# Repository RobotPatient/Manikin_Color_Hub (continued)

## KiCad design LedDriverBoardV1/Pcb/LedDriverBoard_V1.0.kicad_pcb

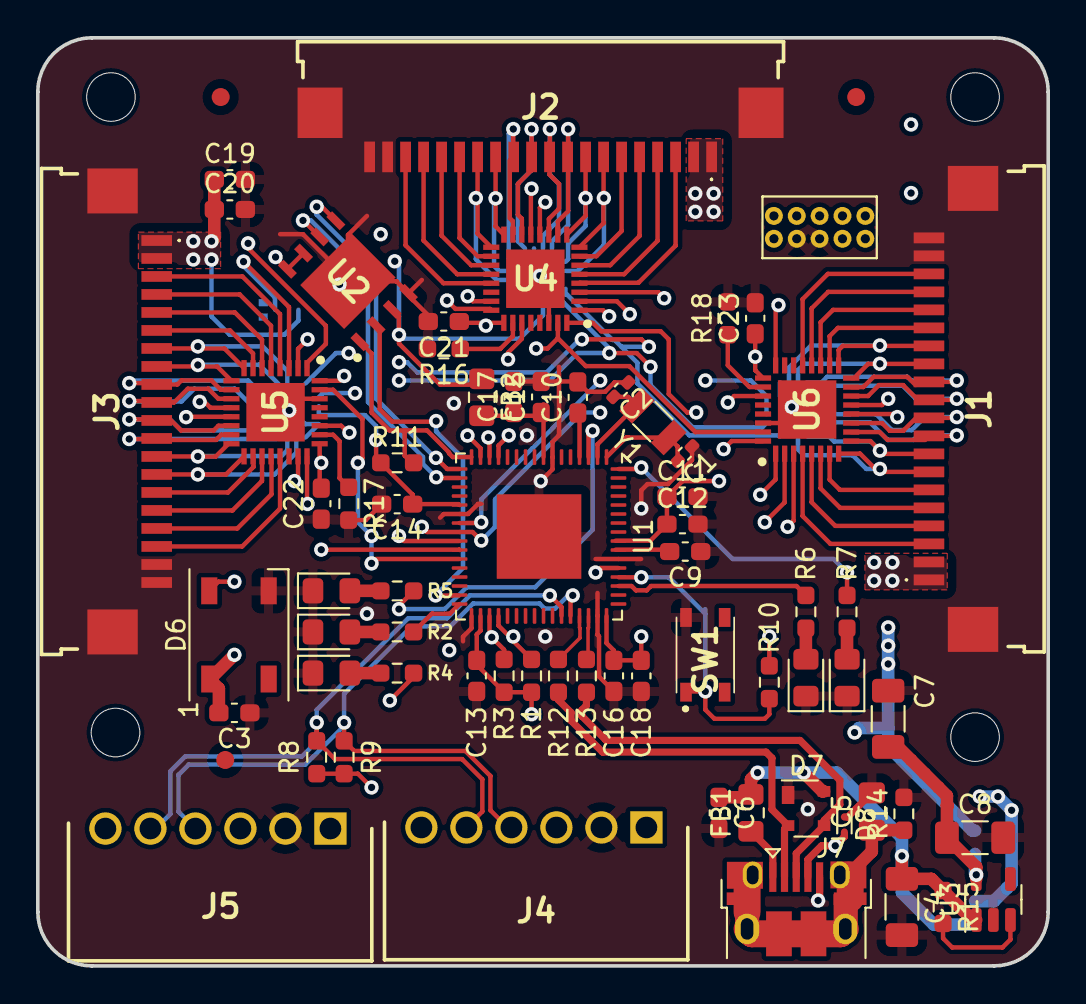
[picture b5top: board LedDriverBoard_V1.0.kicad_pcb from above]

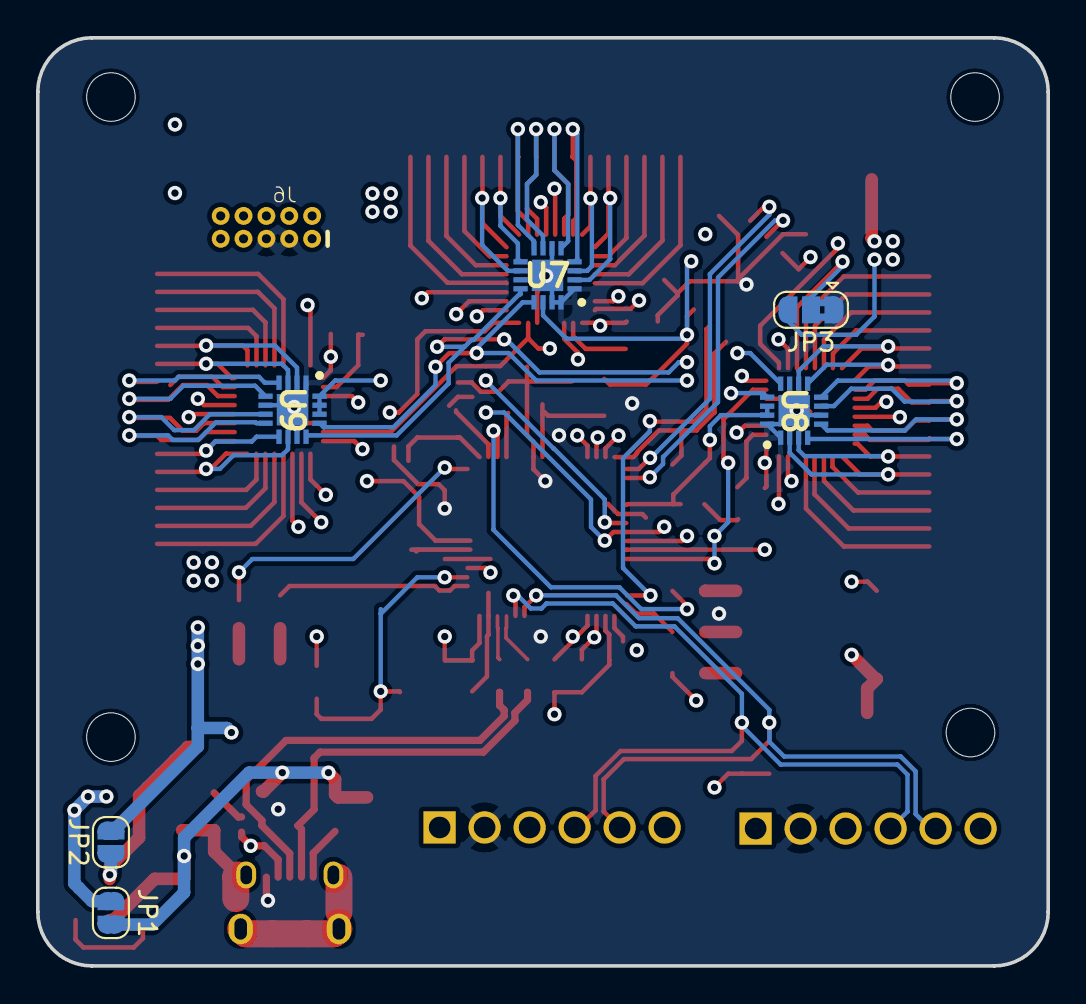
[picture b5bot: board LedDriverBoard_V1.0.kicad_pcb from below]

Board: 4 copper layers, 56.1 x 51.6 mm, 79 parts (6 on the bottom side), 98 nets.

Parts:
C1, C2: 22pF; C_0402_1005Metric_Pad0.74x0.62mm_HandSolder
C3, C10: 1uF; C_0603_1608Metric_Pad1.08x0.95mm_HandSolder
C4, C7: 10uF; C_1206_3216Metric_Pad1.33x1.80mm_HandSolder
C5: 4.7nF 1kV; C_0805_2012Metric_Pad1.18x1.45mm_HandSolder
C6: 100uF; C_0603_1608Metric_Pad1.08x0.95mm_HandSolder
C8: 1uF; C_1206_3216Metric_Pad1.33x1.80mm_HandSolder
C9, C12, C17, C18: 10uF; C_0603_1608Metric_Pad1.08x0.95mm_HandSolder
C11, C13, C14, C15, C16, C19, C21, C22, C23: 100nF; C_0603_1608Metric_Pad1.08x0.95mm_HandSolder
C20: 4.7uF; C_0603_1608Metric_Pad1.08x0.95mm_HandSolder
D1: BLUE; LED_0805_2012Metric_Pad1.15x1.40mm_HandSolder
D2, D4: GREEN; LED_0805_2012Metric_Pad1.15x1.40mm_HandSolder
D3: RED; LED_0805_2012Metric_Pad1.15x1.40mm_HandSolder
D5: ORANGE; LED_0805_2012Metric_Pad1.15x1.40mm_HandSolder
D6: WS2812B; LED_WS2812B_PLCC4_5.0x5.0mm_P3.2mm
D7: PRTR5V0U2X; SOT-143
D8: ESD9B5.0ST5G; D_SOD-923
FB1, FB2: FerriteBead; L_0805_2012Metric_Pad1.15x1.40mm_HandSolder
FID1, FID2, FID3: Fiducial; Fiducial_1mm_Mask2mm
H1, H2, H3, H4: MountingHole; MountingHole_2.7mm_M2.5_DIN965
J1, J2, J3: FFC3B11-20-T; FFC3B1120T
J4, J5: 1778667; SHDRRA6W70P0X250_1X6_1670X750X510P
J6: CORTEX_DEBUGPTH; 2X5-PTH-1.27MM
J7: USB_B_Mini; USB_Micro-B_Amphenol_10103594-0001LF_Horizontal
JP1, JP2: Jumper_2_Open; SolderJumper-2_P1.3mm_Open_RoundedPad1.0x1.5mm
JP3: Jumper_3_Bridged12; SolderJumper-3_P1.3mm_Bridged2Bar12_RoundedPad1.0x1.5mm
R1, R3, R8, R9: 4.7k; R_0603_1608Metric_Pad0.98x0.95mm_HandSolder
R2, R5, R7: 330; R_0603_1608Metric_Pad0.98x0.95mm_HandSolder
R4, R6: 470; R_0603_1608Metric_Pad0.98x0.95mm_HandSolder
R10, R11: 10k; R_0603_1608Metric_Pad0.98x0.95mm_HandSolder
R12, R13: 27; R_0603_1608Metric_Pad0.98x0.95mm_HandSolder
R14: 1M; R_0603_1608Metric_Pad0.98x0.95mm_HandSolder
R15: 100k; R_0603_1608Metric_Pad0.98x0.95mm_HandSolder
R16, R17, R18: 2k; R_0603_1608Metric_Pad0.98x0.95mm_HandSolder
SW1: SW_Push; PTS810SJG250SMTRLFS
U1: ATSAMD21J18A-M; QFN-64-1EP_9x9mm_P0.5mm_EP4.7x4.7mm
U2: IS25LP032D-JLLE; SON127P600X500X75-9N-D
U3: AP2112K-3.3; SOT-23-5
U4, U5, U6: TLC59401RHBR; QFN50P500X500X100-33N-D
U7, U8, U9: PCA9670BS,118; QFN50P300X300X100-17N-D
Y1: 32.768mHz; Crystal_SMD_3215-2Pin_3.2x1.5mm

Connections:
+3V3: C3.2, C11.1, C12.1, C13.1, C14.1, C16.1, C18.1, D6.1 (VDD), FB2.1, J4.3, J5.3, J6.1 (VCC), JP2.2 (B), R1.1, R3.2, R4.1, R8.1, R9.2, R10.2, R11.1, U1.21 (VDDIO), U1.34 (VDDIO), U1.48 (VDDIO), U1.56 (VDDIN), U2.3 (~WP(IO2)), U2.7 (~HOLD(IO3)), U2.8 (VCC), U7.14 (VDD), U8.14 (VDD), U8.15 (AD0), U9.14 (VDD), U9.15 (AD0), U9.16 (AD1)
+5V: C19.1, C20.1, C21.1, C22.1, C23.1, J1.1, J1.2, J2.1, J2.2, J3.1, J3.2, J4.1, J5.1, JP1.2 (B), JP3.3 (B), U4.25 (TEST), U4.27 (VCC), U5.25 (TEST), U5.27 (VCC), U6.25 (TEST), U6.27 (VCC)
/AREF: C10.1, U1.4 (PA03)
/D2_FLASHMISO: U1.31 (PA14), U2.2 (SO(IO1))
/D3_FLASHSCK: U1.18 (PA09), U2.6 (SCK)
/D4_FLASHMOSI: U1.17 (PA08), U2.5 (SI(IO0))
/D5_HEALTH: R2.1, U1.32 (PA15)
/D8_NEOPIXEL: D6.4 (DIN), U1.15 (PA06)
/D14_HB: R5.1, U1.3 (PA02)
/INT4: J4.6, U1.13 (PA04)
/INT5: J5.6, U1.14 (PA05)
/LED1-0: J2.3, U4.4 (OUT0)
/LED1-1: J2.4, U4.5 (OUT1)
/LED1-2: J2.5, U4.6 (OUT2)
/LED1-3: J2.6, U4.7 (OUT3)
/LED1-4: J2.7, U4.8 (OUT4), U7.10 (P7)
/LED1-5: J2.8, U4.9 (OUT5), U7.9 (P6)
/LED1-6: J2.9, U4.10 (OUT6), U7.8 (P5)
/LED1-7: J2.10, U4.11 (OUT7), U7.7 (P4)
/LED1-8: J2.11, U4.14 (OUT8), U7.5 (P3)
/LED1-9: J2.12, U4.15 (OUT9), U7.4 (P2)
/LED1-10: J2.13, U4.16 (OUT10), U7.3 (P1)
/LED1-11: J2.14, U4.17 (OUT11), U7.2 (P0)
/LED1-12: J2.15, U4.18 (OUT12)
/LED1-13: J2.16, U4.19 (OUT13)
/LED1-14: J2.17, U4.20 (OUT14)
/LED1-15: J2.18, U4.21 (OUT15)
/LED2-0: J3.3, U5.4 (OUT0)
/LED2-1: J3.4, U5.5 (OUT1)
/LED2-2: J3.5, U5.6 (OUT2)
/LED2-3: J3.6, U5.7 (OUT3)
/LED2-4: J3.7, U5.8 (OUT4), U8.10 (P7)
/LED2-5: J3.8, U5.9 (OUT5), U8.9 (P6)
/LED2-6: J3.9, U5.10 (OUT6), U8.8 (P5)
/LED2-7: J3.10, U5.11 (OUT7), U8.7 (P4)
/LED2-8: J3.11, U5.14 (OUT8), U8.5 (P3)
/LED2-9: J3.12, U5.15 (OUT9), U8.4 (P2)
/LED2-10: J3.13, U5.16 (OUT10), U8.3 (P1)
/LED2-11: J3.14, U5.17 (OUT11), U8.2 (P0)
/LED2-12: J3.15, U5.18 (OUT12)
/LED2-13: J3.16, U5.19 (OUT13)
/LED2-14: J3.17, U5.20 (OUT14)
/LED2-15: J3.18, U5.21 (OUT15)
/LED3-0: J1.3, U6.4 (OUT0)
/LED3-1: J1.4, U6.5 (OUT1)
/LED3-2: J1.5, U6.6 (OUT2)
/LED3-3: J1.6, U6.7 (OUT3)
/LED3-4: J1.7, U6.8 (OUT4), U9.10 (P7)
/LED3-5: J1.8, U6.9 (OUT5), U9.9 (P6)
/LED3-6: J1.9, U6.10 (OUT6), U9.8 (P5)
/LED3-7: J1.10, U6.11 (OUT7), U9.7 (P4)
/LED3-8: J1.11, U6.14 (OUT8), U9.5 (P3)
/LED3-9: J1.12, U6.15 (OUT9), U9.4 (P2)
/LED3-10: J1.13, U6.16 (OUT10), U9.3 (P1)
/LED3-11: J1.14, U6.17 (OUT11), U9.2 (P0)
/LED3-12: J1.15, U6.18 (OUT12)
/LED3-13: J1.16, U6.19 (OUT13)
/LED3-14: J1.17, U6.20 (OUT14)
/LED3-15: J1.18, U6.21 (OUT15)
/LEDBLANK: U1.27 (PB14), U4.31 (BLANK), U5.31 (BLANK), U6.31 (BLANK)
/LEDGSLCK: U1.26 (PB13), U4.24 (GSCLK), U5.24 (GSCLK), U6.24 (GSCLK)
/LEDSCLK: U1.24 (PB11), U4.1 (SCLK), U5.1 (SCLK), U6.1 (SCLK)
/LEDSIN: U1.23 (PB10), U4.2 (SIN)
/LEDXLAT: U1.25 (PB12), U4.32 (XLAT), U5.32 (XLAT), U6.32 (XLAT)
/LedDriver/LEDMODE: JP3.2 (C), U4.3 (MODE), U5.3 (MODE), U6.3 (MODE)
/LedDriver/LEDSOUT-1: U4.23 (SOUT), U5.2 (SIN)
/LedDriver/LEDSOUT-2: U5.23 (SOUT), U6.2 (SIN)
/PA0_XTAL: C1.2, U1.1 (PA00), Y1.2
/PA1_XTAL: C2.2, U1.2 (PA01), Y1.1
/PA7_FLASH_CS: R11.2, U1.16 (PA07), U2.1 (~CE)
/Power/3.3v: C7.1, C8.1, JP2.1 (A), U3.5 (VOUT)
/Power/SHIELD: C5.1, J7.6 (Shield), R14.1
/RXLED: R7.1, U1.64 (PB03)
/SCL: J4.4, J5.4, R8.2, U1.44 (PA23)
/SCL_IO: R1.2, U1.36 (PA17), U7.12 (SCL), U8.12 (SCL), U9.12 (SCL)
/SDA: J4.5, J5.5, R9.1, U1.43 (PA22)
/SDA_IO: R3.1, U1.35 (PA16), U7.13 (SDA), U8.13 (SDA), U9.13 (SDA)
/TXLED: R6.1, U1.51 (PA27)
/USBHOSTEN: D8.2 (A2), J7.4 (ID), U1.53 (PA28)
/USB_D+: D7.3 (I/O2), J7.3 (D+), R13.1
/USB_D-: D7.2 (I/O1), J7.2 (D-), R12.1
/USB_TERM_D+: R13.2, U1.46 (PA25)
/USB_TERM_D-: R12.2, U1.45 (PA24)
/VDDANA: C15.1, C17.1, FB2.2, U1.8 (VDDANA)
/VDDCORE: C9.2, U1.55 (VDDCORE)
/~RESET: R10.1, SW1.1, U1.52 (~RESET)
GNDD: C1.1, C2.1, C3.1, C4.2, C5.2, C6.2, C7.2, C8.2, C9.1, C10.2, C11.2, C12.2, C13.2, C14.2, C15.2, C16.2, C17.2, C18.2, C19.2, C20.2, C21.2, C22.2, C23.2, D1.1 (K), D2.1 (K), D3.1 (K), D4.1 (K), D5.1 (K), D6.3 (VSS), D7.1 (GND), D8.1 (A1), J1.19, J1.20, J1.MP1, J1.MP2, J2.19, J2.20, J2.MP1, J2.MP2, J3.19, J3.20, J3.MP1, J3.MP2, J4.2, J5.2, J6.3 (GND), J6.5 (GND), J7.5 (GND), JP3.1 (A), R14.2, R16.2, R17.2, R18.2, SW1.2, U1.7 (GNDANA), U1.22 (GND), U1.33 (GND), U1.47 (GND), U1.54 (GND), U1.65 (EP), U2.4 (GND), U2.9 (EP), U3.2 (GND), U4.30 (GND), U4.33 (EP), U5.30 (GND), U5.33 (EP), U6.30 (GND), U6.33 (EP), U7.1 (AD2), U7.6 (VSS), U7.15 (AD0), U7.16 (AD1), U7.17 (EP), U8.1 (AD2), U8.6 (VSS), U8.16 (AD1), U8.17 (EP), U9.1 (AD2), U9.6 (VSS), U9.17 (EP)
unnamed: D1.2 (A), R2.2
unnamed: D2.2 (A), R4.2
unnamed: D3.2 (A), R5.2
unnamed: D4.2 (A), R6.2
unnamed: D5.2 (A), R7.2
unnamed: FB1.1, J7.1 (VBUS)
unnamed: R15.2, U3.3 (EN)
unnamed: R16.1, U4.26 (IREF)
unnamed: R17.1, U5.26 (IREF)
unnamed: R18.1, U6.26 (IREF)
VBUS: C4.1, C6.1, D7.4 (VCC), FB1.2, JP1.1 (A), R15.1, U3.1 (VIN)

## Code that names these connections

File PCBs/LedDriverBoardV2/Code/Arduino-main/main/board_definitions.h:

#ifndef BOARD_DEFINITIONS_H
#define BOARD_DEFINITIONS_H

#define LED_STAT 34 //PA6
#define STAT_CNT 1  // one neoPixel for status led
#define STAT_BRT 10 // Brightness of status neoPixel

#define LED_SN 26 // PA2
#define LED_HB 13 // PA15
#define LED_TX 17 // PB3
#define LED_RX 15  // PA27

#define LEDSTRIP_1 45 // PB16
#define LEDSTRIP_2 41 // PA19 
#define LEDSTRIP_3 47 // PB17
#define LEDSTRIP_4 8  // PA20

#define STRIP1_CNT 5  // Amount of neoPixels for ledstrip 1
#define STRIP2_CNT 5  // Amount of neoPixels for ledstrip 2
#define STRIP3_CNT 5  // Amount of neoPixels for ledstrip 3
#define STRIP4_CNT 5  // Amount of neoPixels for ledstrip 4

#define STRIP1_BRT 10 // Brightness of neoPixels for ledstrip 1
#define STRIP2_BRT 10 // Brightness of neoPixels for ledstrip 2
#define STRIP3_BRT 10 // Brightness of neoPixels for ledstrip 3
#define STRIP4_BRT 10 // Brightness of neoPixels for ledstrip 4

#define BTN1 21  // PB31 //!
#define BTN2 22  // PB0
#define BTN3 23  // PB1

#define MAIN_SDA 29  // PA22
#define MAIN_SDO 28  // PA23
#define MAIN_INT4 35 // PA4
#define MAIN_INT5 37 // PA5

#define IOMUX_SDA 40 // PA16
#define IOMUX_SDO 42 // PA17

#define AUX_SDA 20 // PA12
#define AUX_SDO 21 // PA13

#define LED_SIN 31   // PB10
#define LED_CLK 30   // PB11
#define LED_LAT 18   // PB12
#define LED_GCLK 19  // PB13
#define LED_BLANK 10 // PB14

#define FLASH_CLK 32  // PA9
#define FLASH_MISO 51 // PA14
#define FLASH_MOSI 33 // PA8
#define FLASH_CS 36   // PA7

#define USB_DP 24 // PA24
#define USB_DM 25 // PA25

void initPins()
{
  pinMode(LED_STAT, OUTPUT);

  pinMode(LED_HB, OUTPUT);
  pinMode(LED_SN, OUTPUT);
  pinMode(LED_TX, OUTPUT);
  pinMode(LED_RX, OUTPUT);

  pinMode(LEDSTRIP_1, OUTPUT);
  pinMode(LEDSTRIP_2, OUTPUT);
  pinMode(LEDSTRIP_3, OUTPUT);
  pinMode(LEDSTRIP_4, OUTPUT);

  pinMode(BTN1, INPUT_PULLUP);
  pinMode(BTN2, INPUT_PULLUP);
  pinMode(BTN3, INPUT_PULLUP);
}

#endif //BOARD_DEFINITIONS_H

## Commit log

2024-01-15 Add submodules
2024-01-16 Add final documents
2024-01-16 Update file structure
